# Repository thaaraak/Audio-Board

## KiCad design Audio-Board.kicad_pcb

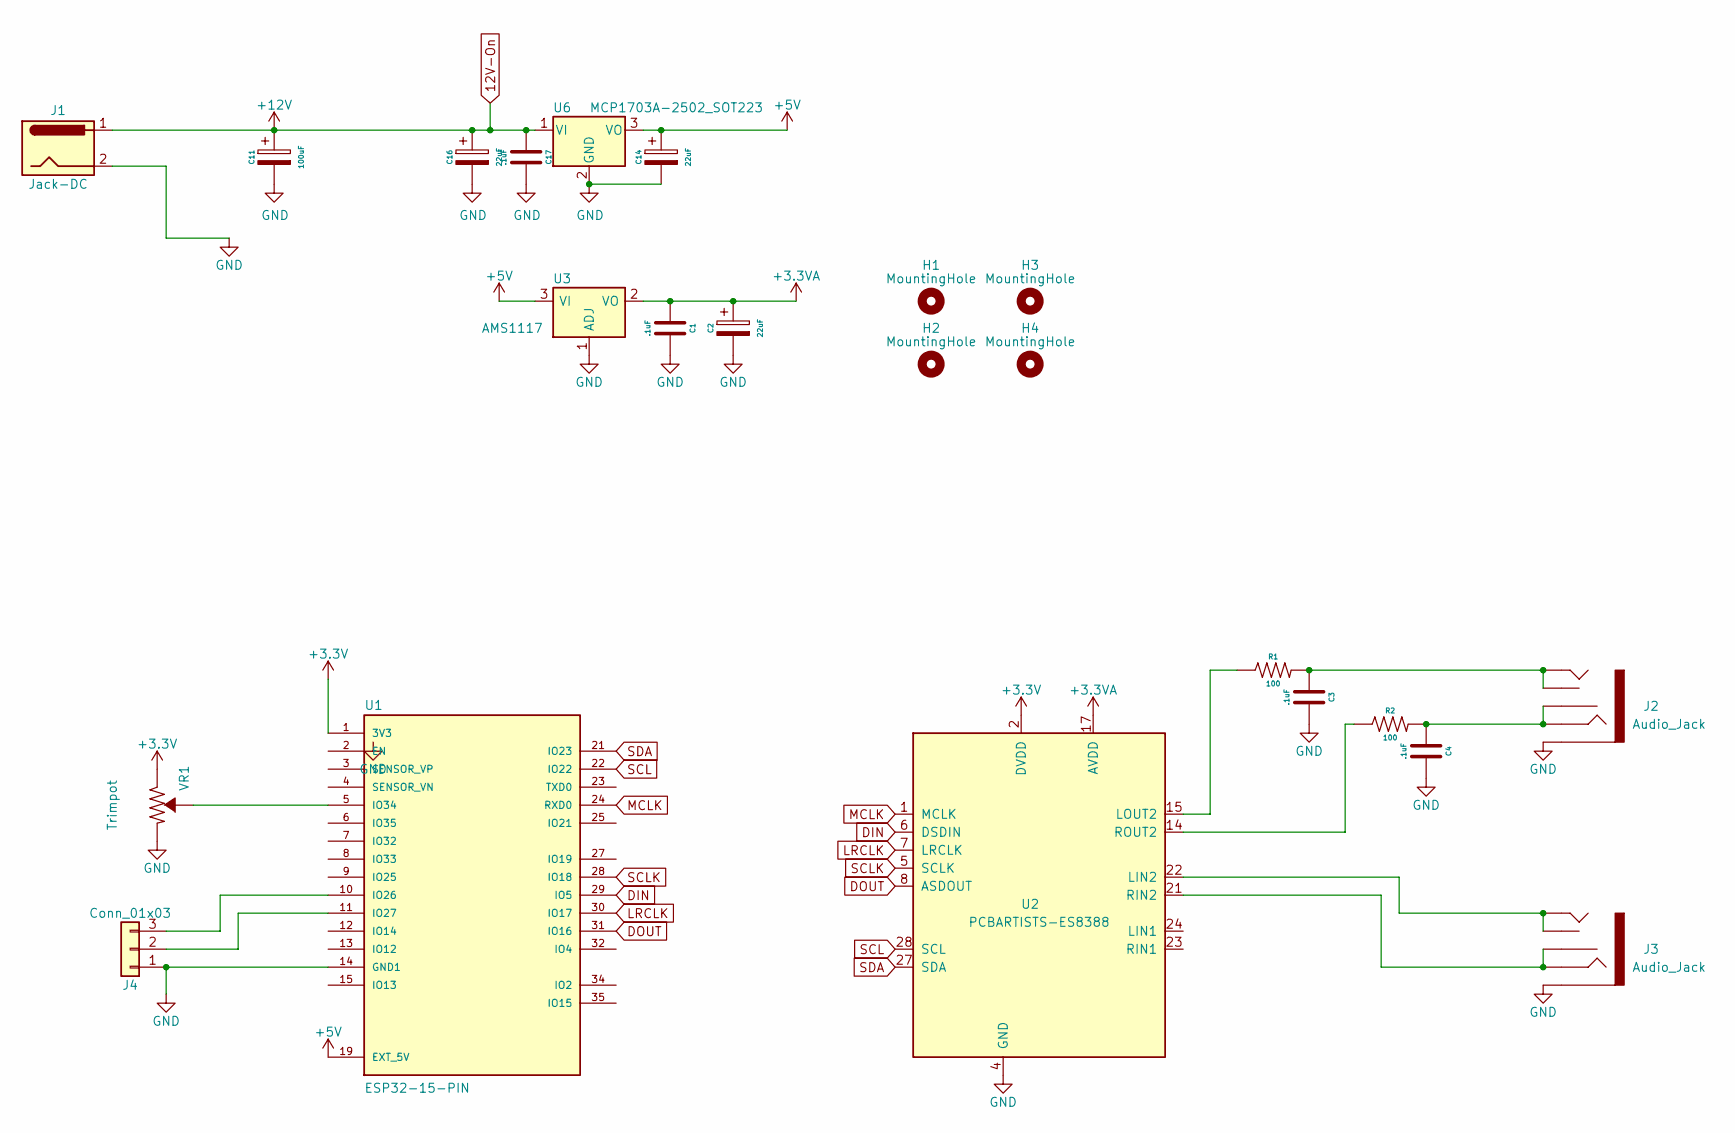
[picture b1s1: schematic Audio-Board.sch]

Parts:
C1, C3, C4, C17: .1uF; Capacitor 0805
C2, C14, C16: 22uF; Cap_4x5.4
C11: 100uF; Cap_6.3x5.4
H1, H2, H3, H4: MountingHole; MountingHole_2.7mm_M2.5_Pad
J1: Jack-DC; BarrelJack_Horizontal
J2, J3: Audio_Jack
J4: Conn_01x03; PinHeader_1x03_P2.54mm_Vertical
R1, R2: 100; Resistor 0805
U1: ESP32-15-PIN; ESP32-15Pin; PARTREV 4
U2: PCBARTISTS-ES8388; PCBArtist-ES8388
U3: AMS1117; SOT-223-3_TabPin2
U6: MCP1703A-2502_SOT223; TO-252-3_TabPin2
VR1: Trimpot; Trimpot Vertical

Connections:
12V-On: C11.1, C16.1, C17.1, J1.1, U6.1 (VI)
+3.3VA: C1.1, C2.1, U2.17 (AVDD), U3.2 (VO)
+3V3: U1.1 (3V3), U2.2 (DVDD), VR1.1 (CW)
+5V: C14.1, U1.19 (EXT_5V), U3.3 (VI), U6.3 (VO)
DIN: U1.29 (IO5), U2.6 (DSDIN)
DOUT: U1.31 (IO16), U2.8 (ASDOUT)
GND: C1.2, C2.2, C3.2, C4.2, C11.2, C14.2, C16.2, C17.2, J1.2, J2.SLEEVE, J3.SLEEVE, J4.1, U1.14 (GND1), U2.4 (GND), U3.1 (ADJ), U6.2 (GND), VR1.3 (CCW)
LRCLK: U1.30 (IO17), U2.7 (LRCLK)
MCLK: U1.24 (RXD0), U2.1 (MCLK)
unnamed: C3.1, J2.TIP, J2.TSH, R1.2
unnamed: C4.1, J2.RING, J2.RSH, R2.2
unnamed: J3.RING, J3.RSH, U2.21 (RIN2)
unnamed: J3.TIP, J3.TSH, U2.22 (LIN2)
unnamed: J4.2, U1.11 (IO27)
unnamed: J4.3, U1.10 (IO26)
unnamed: R1.1, U2.15 (LOUT2)
unnamed: R2.1, U2.14 (ROUT2)
unnamed: U1.5 (IO34), VR1.2 (WIPER)
SCL: U1.22 (IO22), U2.28 (SCL)
SCLK: U1.28 (IO18), U2.5 (SCLK)
SDA: U1.21 (IO23), U2.27 (SDA)

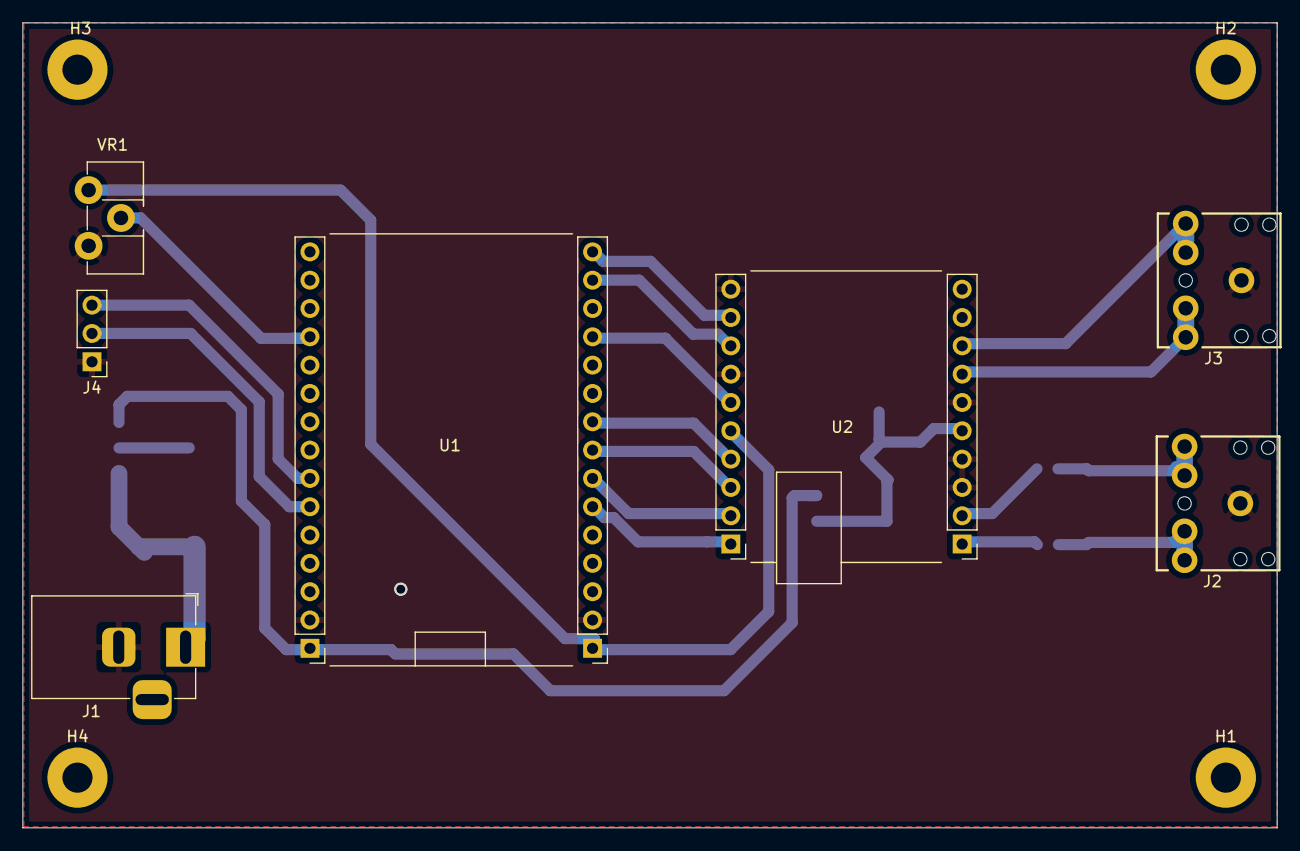
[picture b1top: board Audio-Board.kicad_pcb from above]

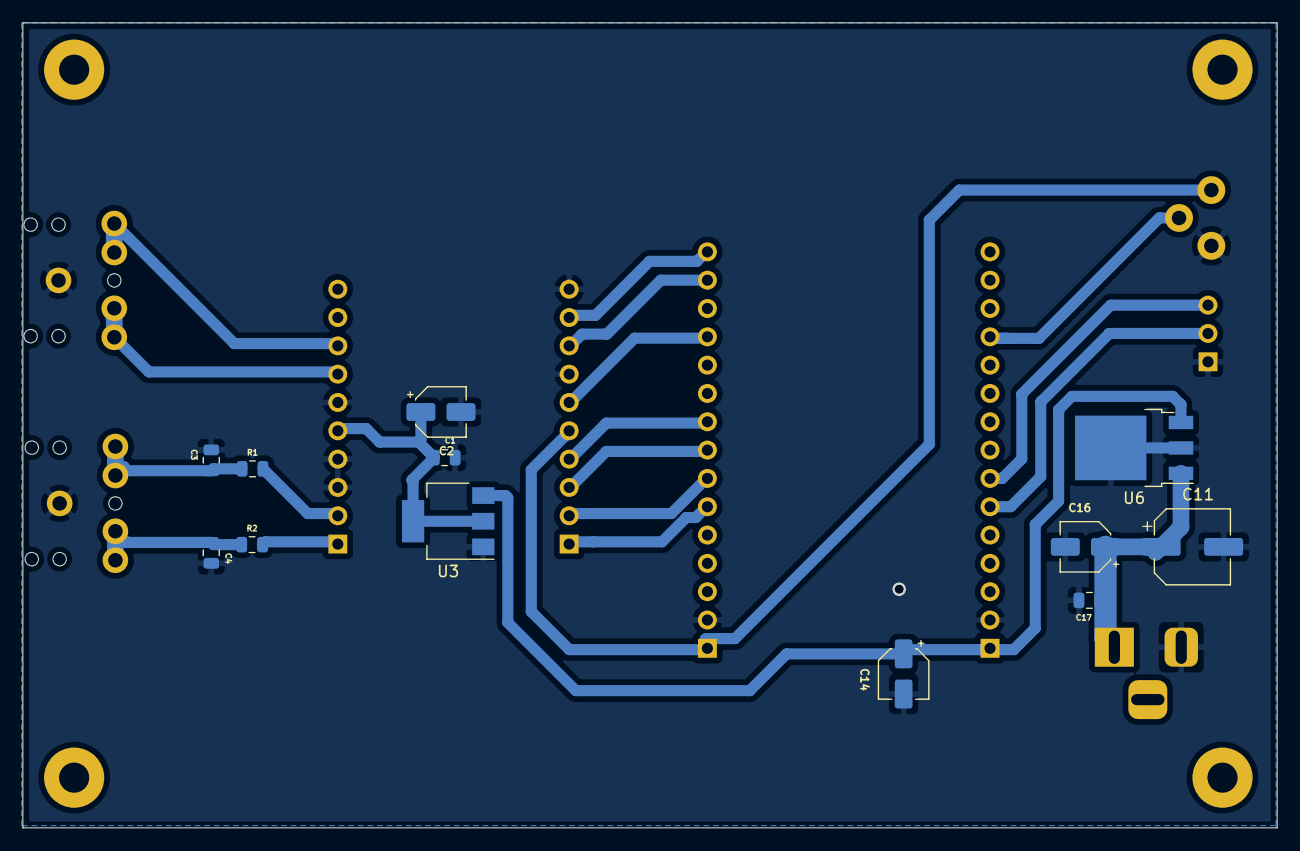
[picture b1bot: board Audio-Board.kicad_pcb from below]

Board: 2 copper layers, 112.5 x 72.2 mm, 23 parts (12 on the bottom side), 21 nets.
